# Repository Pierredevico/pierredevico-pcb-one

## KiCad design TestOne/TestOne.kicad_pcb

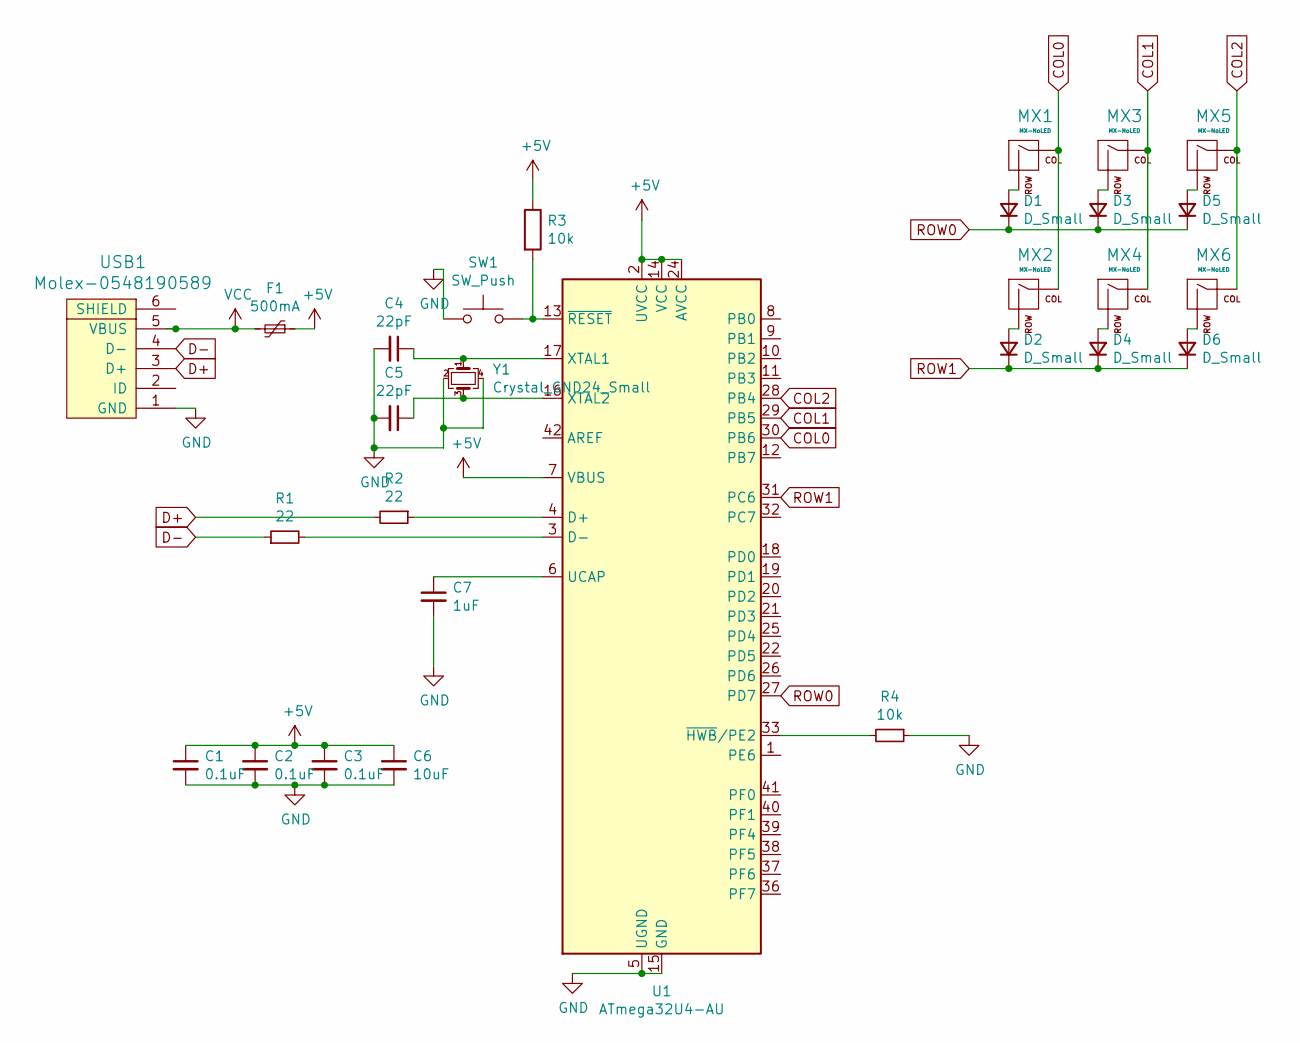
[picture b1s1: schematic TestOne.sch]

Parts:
C1, C2, C3: 0.1uF; C_0805_2012Metric
C4, C5: 22pF; C_0805_2012Metric
C6: 10uF; C_0805_2012Metric
C7: 1uF; C_0805_2012Metric
D1, D2, D3, D4, D5, D6: D_Small; D_SOD-123
F1: 500mA; Fuse_1206_3216Metric
MX1, MX2, MX3, MX4, MX5, MX6: MX-NoLED; MX-1U
R1, R2: 22; R_0805_2012Metric
R3, R4: 10k; R_0805_2012Metric
SW1: SW_Push; SKQG-1155865
U1: ATmega32U4-AU; TQFP-44_10x10mm_P0.8mm
USB1: Molex-0548190589
Y1: Crystal_GND24_Small; Crystal_SMD_3225-4Pin_3.2x2.5mm

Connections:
+5V: C1.1, C2.1, C3.1, C6.1, F1.1, R3.1, U1.2 (UVCC), U1.7 (VBUS), U1.14 (VCC), U1.24 (AVCC), U1.34 (VCC), U1.44 (AVCC)
COL0: MX1.1 (COL), MX2.1 (COL), U1.30 (PB6)
COL1: MX3.1 (COL), MX4.1 (COL), U1.29 (PB5)
COL2: MX5.1 (COL), MX6.1 (COL), U1.28 (PB4)
D+: R2.2, USB1.3 (D+)
D-: R1.1, USB1.4 (D-)
GND: C1.2, C2.2, C3.2, C4.2, C5.2, C6.2, C7.2, R4.1, SW1.1, U1.5 (UGND), U1.15 (GND), U1.23 (GND), U1.35 (GND), U1.43 (GND), USB1.1 (GND), Y1.2, Y1.4
unnamed: C4.1, U1.17 (XTAL1), Y1.1
unnamed: C5.1, U1.16 (XTAL2), Y1.3
unnamed: C7.1, U1.6 (UCAP)
unnamed: D1.2 (A), MX1.2 (ROW)
unnamed: D2.2 (A), MX2.2 (ROW)
unnamed: D3.2 (A), MX3.2 (ROW)
unnamed: D4.2 (A), MX4.2 (ROW)
unnamed: D5.2 (A), MX5.2 (ROW)
unnamed: D6.2 (A), MX6.2 (ROW)
unnamed: R1.2, U1.3 (D-)
unnamed: R2.1, U1.4 (D+)
unnamed: R3.2, SW1.2, U1.13 (~RESET)
unnamed: R4.2, U1.33 (~HWB~/PE2)
ROW0: D1.1 (K), D3.1 (K), D5.1 (K), U1.27 (PD7)
ROW1: D2.1 (K), D4.1 (K), D6.1 (K), U1.31 (PC6)
VCC: F1.2, USB1.5 (VBUS)

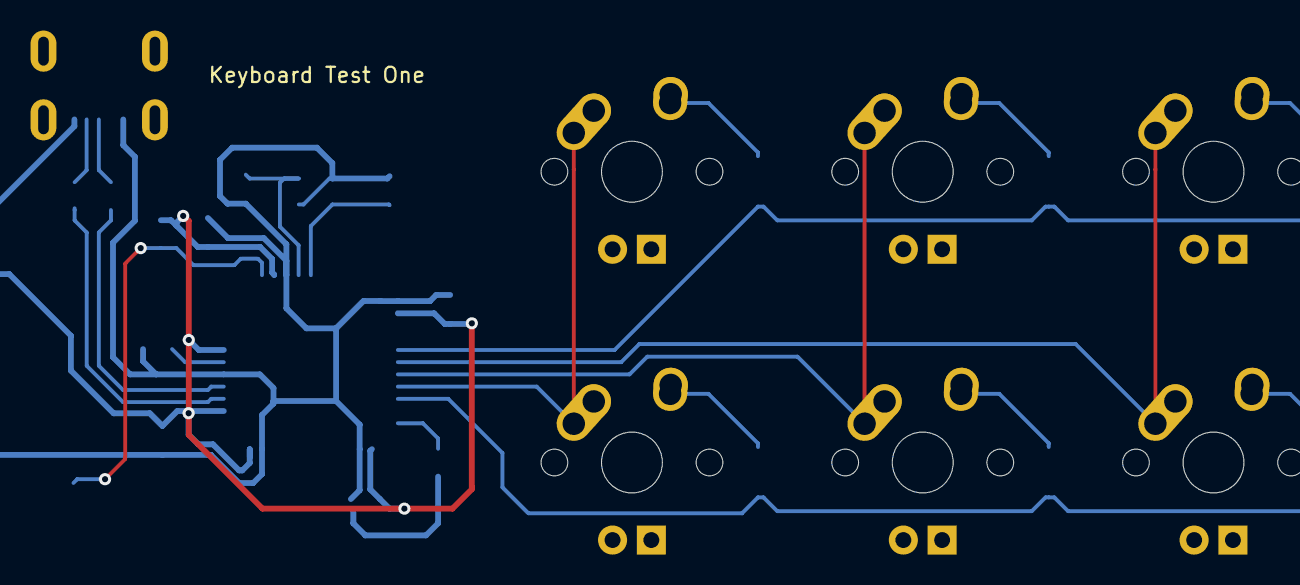
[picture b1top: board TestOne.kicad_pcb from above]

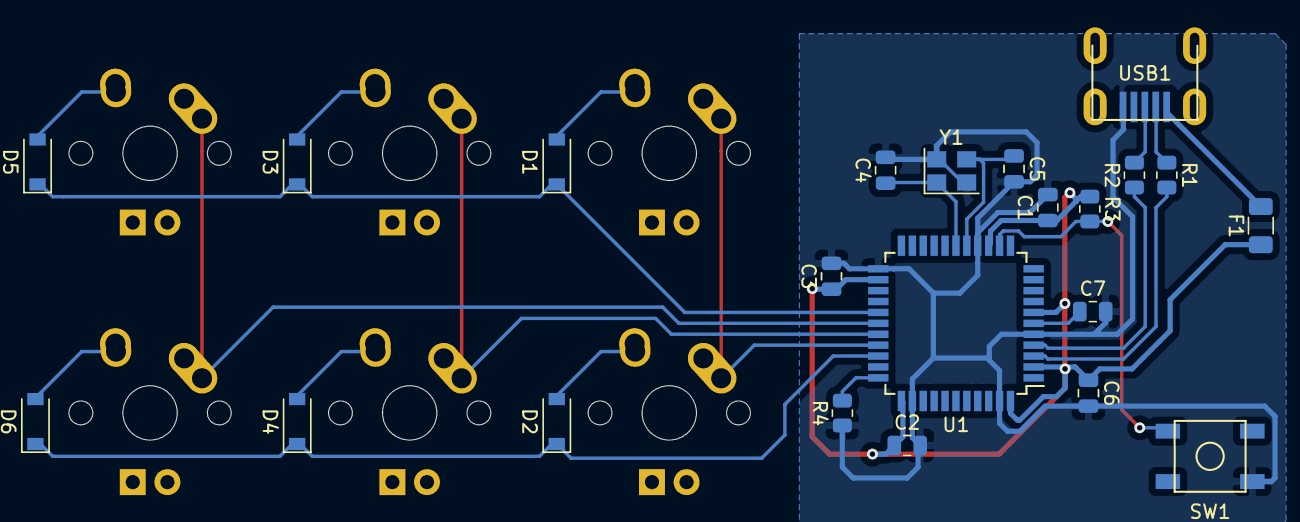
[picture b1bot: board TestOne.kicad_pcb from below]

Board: 2 copper layers, 28 parts (22 on the bottom side), 23 nets.

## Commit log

2021-02-10 initialized project
2021-02-10 Added footprint libraries
2021-02-11 Finished schematic
2021-02-11 Created PCB
2021-02-11 Finished
